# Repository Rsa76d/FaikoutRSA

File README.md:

## Support

You can support this project in many ways, including testing and diagnostics, merge requests, clearly described issues and suggestions, and [buying Faikout boards from us](https://shop.revk.uk?mrlHiG1i). Thank you all for your support. This is open source so others can make and sell (with trademark restrictions). AI based bug reprots or MRs will get you blocked.

# ESP32-Faikout

Everyone knows Daikin make some of the best air conditioners out there, mechanically speaking. Sadly their WiFi control modules are not so good, especially the latest models which are all cloud based, require an internet connection to even work, and are slow.

This code/module provides local control via web interface, MQTT, and HomeAssistant integration, all with no cloud crap.

* There is also a new [Faikout Remote Control](https://remote.revk.uk/) available, BLE linked to the Faikout, with environmental sensors, available now.

I'd like to thank the contributors, but contributions are made and accepted on basis that you issue your contribution under the same GPL licence as the project. Forks are allowed on the basis that your forks are on the same GPL licence as the project.

## Trademark

This is an open source project, but bear in mind you cannot sell boards bearing the Andrews & Arnold Ltd name, the A&A logo, the registered trademark Faikout, the registered trademark AJK logo, or the GS1 allocated EANs assigned to Andrews & Arnold Ltd.

Note the name change from Faikin to Faikout as Daikin complained to Amazon and caused a lot of issues. As such Faikout is now a registered trademark to avoid such issues.

## Further manuals / links

- [Work in progress / release notes](/RevK/ESP32-Faikout/wiki/Work-in-progress)
- [Wiring](/RevK/ESP32-Faikout/wiki/Wiring)
- [Setup](Manuals/Setup.md) Manual
- [Controls](Manuals/Controls.md) Manual
- [Advanced](Manuals/Advanced.md) Manual
- [ESP8266 port](https://github.com/Sonic-Amiga/ESP8266-Faikin) of this code
- [list of supported air-con](/RevK/ESP32-Faikout/wiki/List-of-confirmed-working-air-con-units) WiKi (please update as needed)
- [DoC](Manuals/DoC.md) and Vulnerability disclosure policy
- [S21](Manuals/S21.md) reverse engineered details of `S21` protocol

For support, see issues.

## Safety

Always propely isolate power before opening your air-con. Take care as dangerous voltages. Some connector types have dangerous voltage in operation.

### Ethernet

The Ethernet board has an RJ45 10/100 Ethernet connector for improved reliability and privacy. The Ethernet has an isolating transformer and clearances, but I have to stress **this is a prototype/dev board for specialist/hobbyist use only, and is NOT certified for grid power safety isolation. DO NOT USE WITH X403 CONNECTOR or any connector with dangerous voltages.**

### PoE Ethernet (design not finished)

The PoE Ethernet board has an RJ45 10/100 Ethernet connector for improved reliability and privacy, with PoE power for the Faikout module. The PoE power module has electrical isolation. The board also has opto isolators for the S21 connection, electrically isolating it from the air conditioning unit. This adds extra layers of safety, however I have to stress **this is a prototype/dev board for specialist/hobbyist use only, and is NOT certified for grid power safety isolation.**

Design now works, and boards on order.

## PCB and case

Buy from [shop.revk.uk](https://shop.revk.uk?mrlHiG1i). Also available from a third party in Australia eBay.

New Ethernet option.

New Opto-isiolated PoE Ethernet option.

Board are supplied in a panel, with snap off parts. The basic Faikout board can be two sizes 45x36mm or 40x16mm.

## Why I made this

The history is that, after years of using Daikin air-con in my old home, and using the local http control, in my new house in Wales the WiFi was all cloud based with no local control, and useless, and slow. Just configuring it was a nightmare. I spent all day reverse engineering it and making a new module to provide local control. Pull requests and feature ideas welcome.

This whole project is almost entirely by me, but with some valuable contributions from others (thank you). All of my bits are copyright by me and Andrews & Arnold Ltd who sponsor the whole project, and released under GPL. Whilst not required by the licence, attribution and links would be appreciated if you reuse this.

## How to get one

But also, the PCB designs are published, including production files for [JLCPCB](https://jlcpcb.com). You need to remove trademarks, etc, and you would also need something to program them (TC2030 lead). Obviously you need some experience with PCB ordering and diagnostics if getting your own boards made.

# Set-up

Appears as access point with simple web page to set up on local WiFI. On iPhone the setup page auto-loads.

# Operation

Local interactive web control page using *hostname*.local, no app required, no external internet required.

- [Setup](Manuals/Setup.md) Manual
- [Controls](Manuals/Controls.md) Manual
- [Advanced](Manuals/Advanced.md) Manual

# Design

* KiCad PCB designs included, with JLCPCB production files
* 3D printed case STL files
* Documentation of reverse engineered protocol included

Basically, Daikin have gone all cloudy with the latest WiFi controllers. This module is designed to provide an alternative.

* Simple local web based control with live websocket status, easy to save as desktop icon on a mobile phone
* MQTT reporting and controls
* Works with Home Assistant over MQTT - note Home Assistant can work with HomeKit
* Includes linux mysql/mariadb based logging and graphing tools
* Works with [EnvMon](https://codeberg.org/RevK/ESP32-EnvMon) Environmental Monitor for finer control and status display
* or, works with BlueCoinT and Telink [BLE temperature sensor](Manuals/BLE.md) as a remote reference in an auto mode
* Automatically works out if S21 or X50 protocol (used on bigger/ducted units)
* Backwards compatible direct `/aircon/...` URLs

# Building code yourself

Git clone this `--recursive` to get all the submodules, and it should build with just `make`. There are make targets for other variations, but this hardware is the `make pico` or `make s3` version. The `make` actually runs the normal `idf.py` to build which then uses cmake. `make menuconfig` can be used to fine tune the settings, but the defaults should be mostly sane. `make flash` should work to program. If flashing yourself, you will need a programming lead, e.g. [Tazmotizer](https://codeberg.org/RevK/Tasmotizer-PCB) or similar, and of course the full ESP IDF environment. The latest boards also have 4 pads for direct USB connection to flash with no adaptor. The modules on Amazon come pre-loaded and can upgrade over the air.

The code is normally set up to automatically upgrade the software, checking roughly once a week. You can change this in settings via MQTT.

If you build yourself, you either need no code signing, or your own signing key. This will break auto-updates which try to load my code releases, so you need to adjuist settings `otahost` and `otaauto` accordingly. You can set these in the build config, along with WiFi settings, etc.

## Flashing code

You will need to connect a suitable programming lead. Boards have a tag-connect compatible header for a [TC2030-USB-NL](https://www.tag-connect.com/product/tc2030-usb-nl) lead. Note that the latest boards have test pads on the back which include USB, so you can solder a USB lead if necessary.

See [https://codeberg.org/RevK/ESP32-RevK](https://codeberg.org/RevK/ESP32-RevK) for more details of how to flash the files easily.

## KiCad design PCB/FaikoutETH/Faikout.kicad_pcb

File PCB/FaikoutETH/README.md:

# FaikoutETH

## Trademark

This project is subject to the licence in the LICENCE file, and even if that says it is an open source project, you cannot sell boards or cases bearing the Andrews & Arnold Ltd name, the A&A logo, the registered trademark AJK logo, or other registered trademarks, or any GS1 allocated EANs/barcode assigned to Andrews & Arnold Ltd.

## PCB Designs

These files are for use with [KiCAD](https://www.kicad.org).

- [Faikout](Faikout.kicad_pro)

## 3D

3D case designs are normally automatically created from the PCB so as to ensure correct details and placement of apertures, etc.

|Design|Bottom|Top|Combined|
|------|------|---|--------|
|Faikout||||

## PCB Images Faikout

---

*Auto generated README.md 2026-10-09T09:55:18*

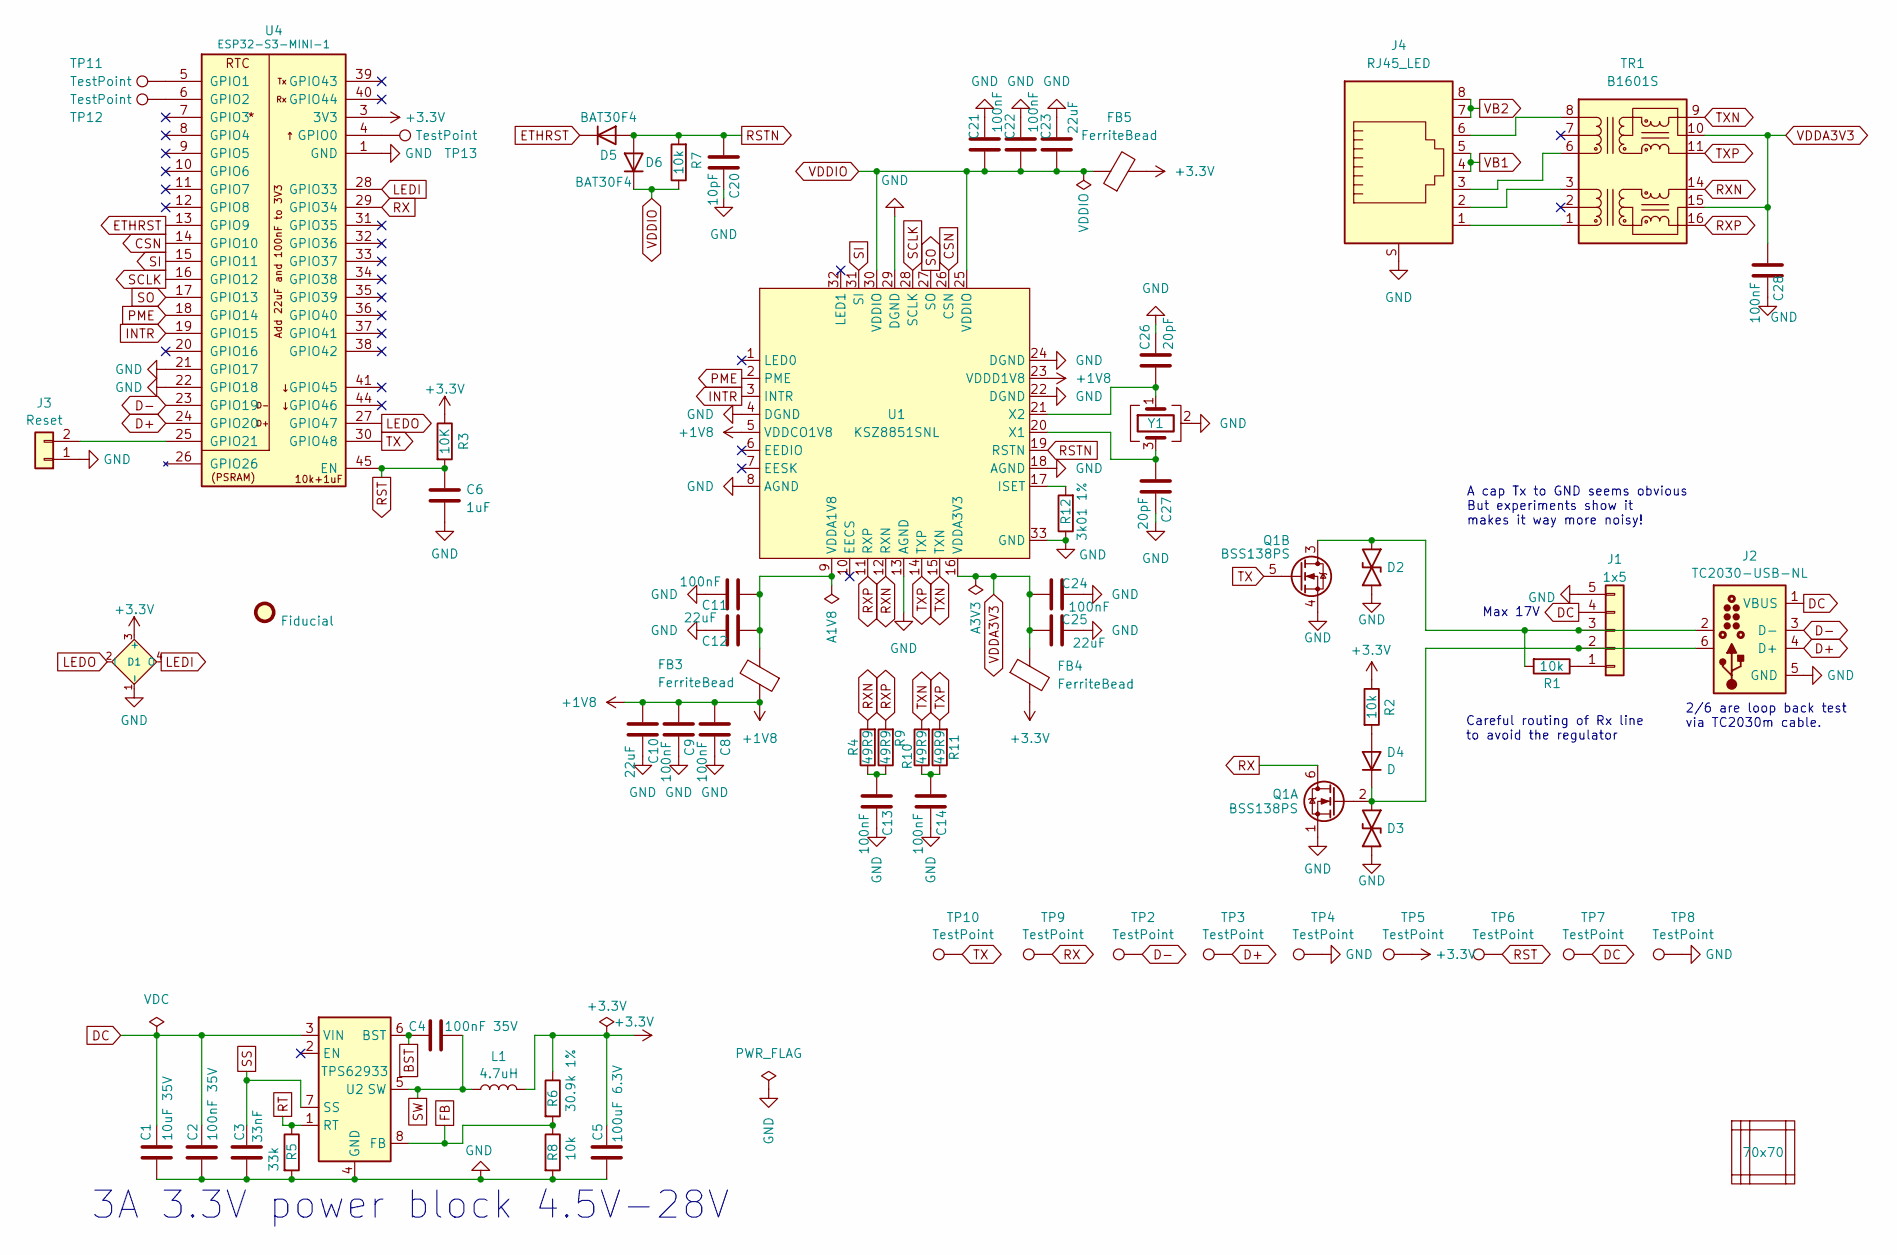
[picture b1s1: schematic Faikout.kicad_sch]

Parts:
C1: 10uF 35V; C_0603; MPN C22367827
C2, C4: 100nF 35V; C_0201; MPN C181043
C3: 33nF; C_0201; MPN C5142554
C5: 100uF 6.3V; C_0805; MPN C141660
C6: 1uF; C_0201; MPN C87143
C8, C9, C11, C13, C14, C21, C22, C24, C28: 100nF; C_0201; MPN C66938
C10, C12, C23, C25: 22uF; C_0402; MPN C105226
C20: 10pF; C_0201; MPN C76921
C26, C27: 20pF; C_0201; MPN C71879
D1: XL-1615RGBC-2812B; SMD1615; MPN C5349954
D2, D3: DFN1006-2L; MPN C5137770
D4: D; D_0402; MPN C28642302
D5, D6: BAT30F4; D_0201; MPN C18197832
FB3, FB4, FB5: FerriteBead; L_0603; MPN C14709
FID2: Fiducial; Fiducial_1mm_Mask2mm
J1: 1x5; JST_EH_S5B-EH_1x05_P2.50mm_Horizontal; MPN C265103
J2: TC2030-USB-NL; Tag-Connect_TC2030-IDC-NL_2x03_P1.27mm_Vertical
J3: Reset; AA-Pad
J4: RJ45_LED; RC01516; MPN C708636
L1: 4.7uH; L_6x6; MPN C32684
PCB1: 70x70; PCB7070
Q1: BSS138PS; SOT-363_SC-70-6; MPN C193381
R1, R2, R7: 10k; R_0201; MPN C138117
R3: 10K; R_0201; MPN C138117
R4, R9, R10, R11: 49R9; R_0201; MPN C100141
R5: 33k; R_0201; MPN C473534
R6: 30.9k 1%; R_0201; MPN C473585
R8: 10k; R_0201; MPN C106225
R12: 3k01 1%; R_0201; MPN C320817
TP2, TP3, TP4, TP5, TP6, TP7, TP8, TP9, TP10, TP11, TP12, TP13: TestPoint; PAD-2mm
TR1: B1601S; MPN C510548
U1: KSZ8851SNL; QFN-32-1EP_5x5mm_P0.5mm_EP3.7x3.7mm-hot; MPN C633272
U2: TPS62933; SOT-583-8; MPN C3200405
U4: ESP32-S3-MINI-1; MPN C3013941
V3, V4, V5, V6, V7: VCUT70N
Y1: Crystal_GND24; Crystal-3.2x2.5; MPN C5155480

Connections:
+1V8: C8.1, C9.1, C10.1, FB3.1, U1.5 (VDDCO1V8), U1.23 (VDDD1V8)
+3.3V: C5.1, D1.3 (+), FB4.2, FB5.2, L1.2, R2.1, R3.1, R6.1, TP5.1 (1_1), U4.3 (3V3)
BST: C4.1, U2.6 (BST)
CSN: U1.26 (CSN), U4.14 (GPIO10)
D+: J2.4 (D+), TP3.1 (1_1), U4.24 (GPIO20)
D-: J2.3 (D-), TP2.1 (1_1), U4.23 (GPIO19)
DC: C1.1, C2.1, J1.4, J2.1 (VBUS), TP7.1 (1_1), U2.3 (VIN)
ETHRST: D5.1 (K), U4.13 (GPIO9)
FB: R6.2, R8.1, U2.8 (FB)
GND: C1.2, C2.2, C3.2, C5.2, C6.2, C8.2, C9.2, C10.2, C11.2, C12.2, C13.2, C14.2, C20.2, C21.2, C22.2, C23.2, C24.2, C25.2, C26.2, C27.2, C28.2, D1.1 (-), D2.1, D3.1, J1.5, J2.5 (GND), J3.1, J4.S, Q1.1 (SN), Q1.4 (DP), R5.2, R8.2, R12.1, TP4.1 (1_1), TP8.1 (1_1), U1.4 (DGND), U1.8 (AGND), U1.13 (AGND), U1.18 (AGND), U1.22 (DGND), U1.24 (DGND), U1.29 (DGND), U1.33 (GND), U2.4 (GND), U4.1 (GND), U4.2 (GND), U4.21 (GPIO17), U4.22 (GPIO18), U4.42 (GND), U4.43 (GND), U4.46 (GND), U4.47 (GND), U4.48 (GND), U4.49 (GND), U4.50 (GND), U4.51 (GND), U4.52 (GND), U4.53 (GND), U4.54 (GND), U4.55 (GND), U4.56 (GND), U4.57 (GND), U4.58 (GND), U4.59 (GND), U4.60 (GND), U4.61 (GND), U4.62 (GND), U4.63 (GND), U4.64 (GND), U4.65 (GND), Y1.2 (G), Y1.4 (G)
INTR: U1.3 (INTR), U4.19 (GPIO15)
LEDI: D1.4 (O), U4.28 (GPIO33)
LEDO: D1.2 (I), U4.27 (GPIO47)
unnamed: C13.1, R4.1, R9.1
unnamed: C14.1, R10.1, R11.1
unnamed: D4.2 (A), R2.2
unnamed: D3.2, D4.1 (K), J1.2, J2.6, Q1.2 (GN)
unnamed: J1.1, R1.1
unnamed: D2.2, J1.3, J2.2, Q1.3 (SP), R1.2
unnamed: J3.2, U4.25 (GPIO21)
unnamed: J4.3, TR1.6 (RD+)
unnamed: J4.6, TR1.8 (RD-)
unnamed: J4.1, TR1.1 (TD+)
unnamed: J4.2, TR1.3 (TD-)
unnamed: R12.2, U1.17 (ISET)
unnamed: C11.1, C12.1, FB3.2, U1.9 (VDDA1V8)
unnamed: C27.1, U1.20 (X1), Y1.3
unnamed: C26.1, U1.21 (X2), Y1.1
unnamed: TP13.1 (1_1), U4.4 (GPIO0)
unnamed: TP11.1 (1_1), U4.5 (GPIO1)
unnamed: TP12.1 (1_1), U4.6 (GPIO2)
PME: U1.2 (PME), U4.18 (GPIO14)
RST: C6.1, R3.2, TP6.1 (1_1), U4.45 (EN)
RSTN: C20.1, D5.2 (A), D6.2 (A), R7.2, U1.19 (RSTN)
RT: R5.1, U2.1 (RT)
RX: Q1.6 (DN), TP9.1 (1_1), U4.29 (GPIO34)
RXN: R4.2, TR1.14 (TX-), U1.12 (RXN)
RXP: R9.2, TR1.16 (TX+), U1.11 (RXP)
SCLK: U1.28 (SCLK), U4.16 (GPIO12)
SI: U1.31 (SI), U4.15 (GPIO11)
SO: U1.27 (SO), U4.17 (GPIO13)
SS: C3.1, U2.7 (SS)
SW: C4.2, L1.1, U2.5 (SW)
TX: Q1.5 (GP), TP10.1 (1_1), U4.30 (GPIO48)
TXN: R10.2, TR1.9 (RX-), U1.15 (TXN)
TXP: R11.2, TR1.11 (RX+), U1.14 (TXP)
VB1: J4.4, J4.5
VB2: J4.7, J4.8
VDDA3V3: C24.1, C25.1, C28.1, FB4.1, TR1.10 (C_RX), TR1.15 (C_TX), U1.16 (VDDA3V3)
VDDIO: C21.1, C22.1, C23.1, D6.1 (K), FB5.1, R7.1, U1.25 (VDDIO), U1.30 (VDDIO)

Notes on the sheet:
Careful routing of Rx line to avoid the regulator
Max 17V
2/6 are loop back test via TC2030m cable.
A cap Tx to GND seems obvious But experiments show it makes it way more noisy!
3A 3.3V power block 4.5V-28V

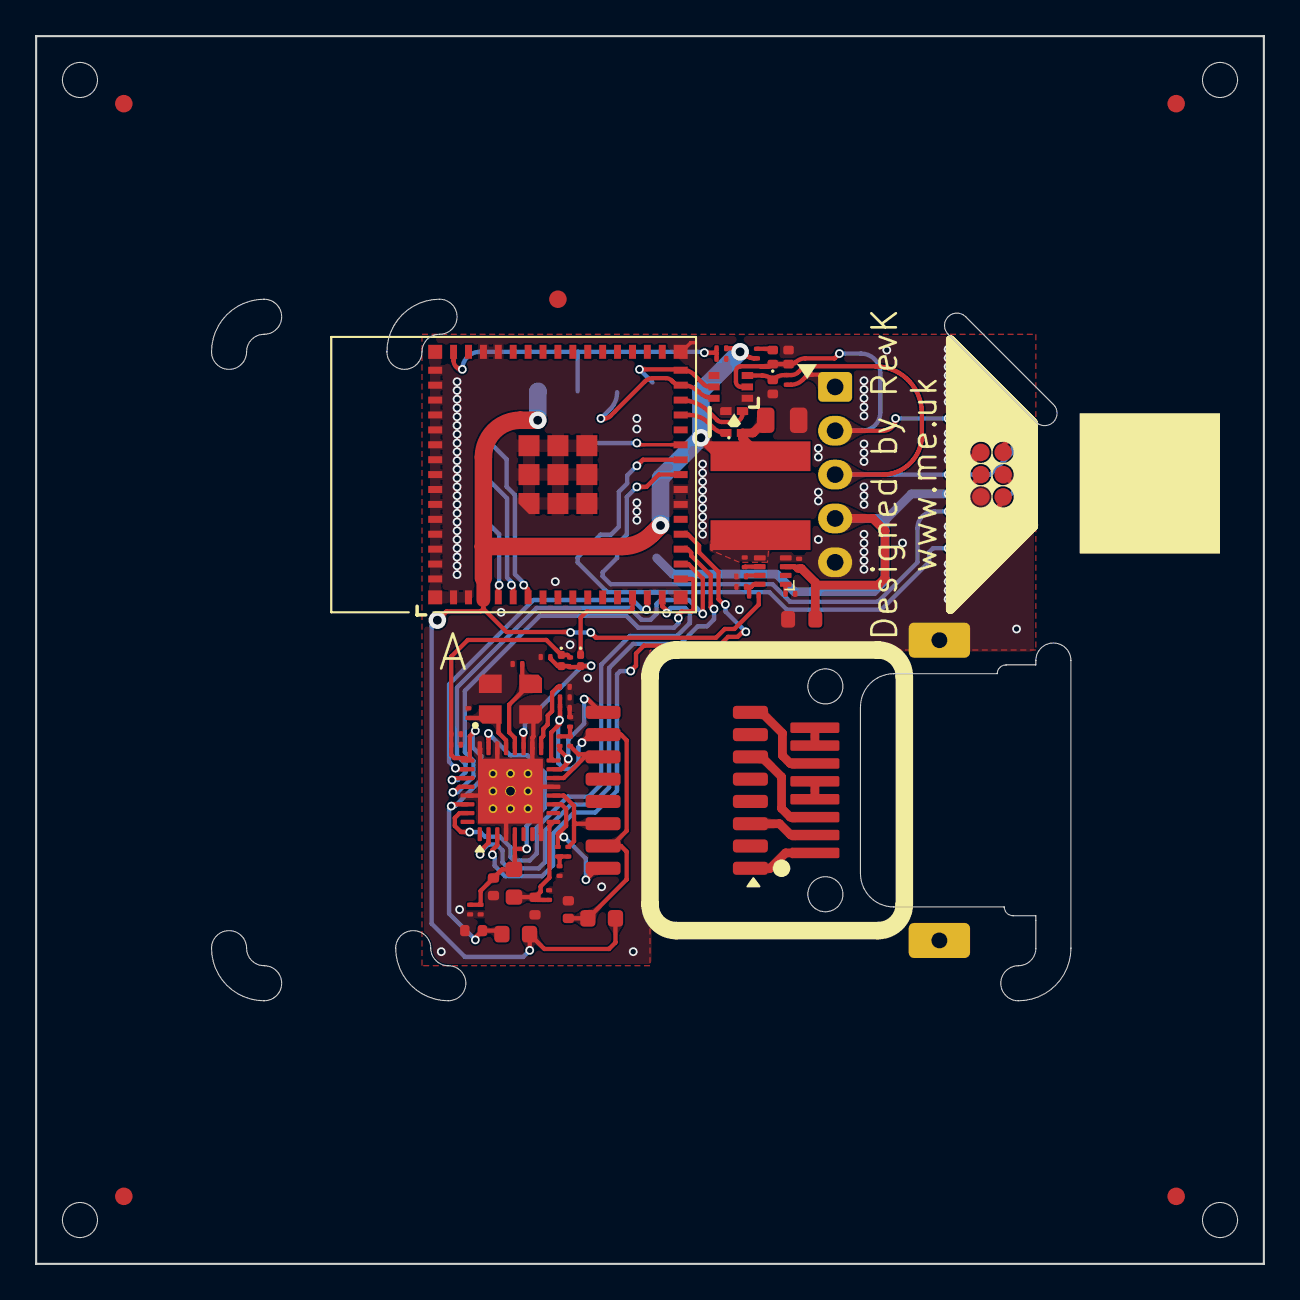
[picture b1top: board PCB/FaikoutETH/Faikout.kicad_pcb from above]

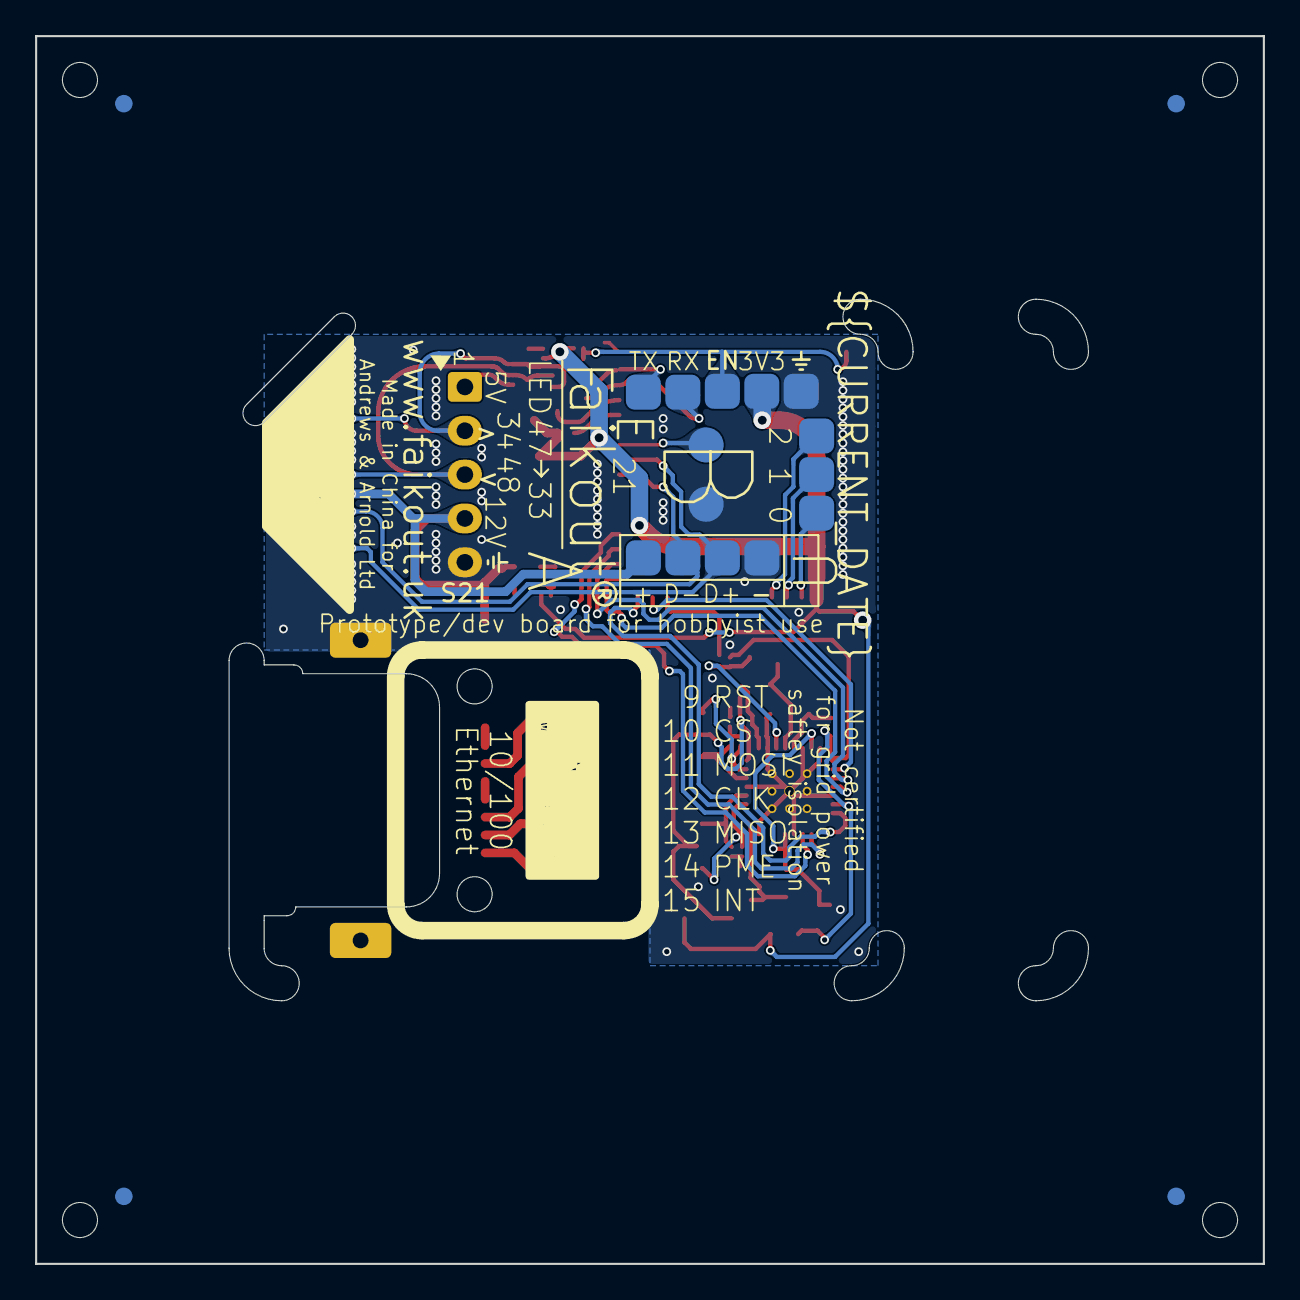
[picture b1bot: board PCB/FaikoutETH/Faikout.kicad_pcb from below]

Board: 2 copper layers, 70.0 x 70.0 mm, 73 parts (14 on the bottom side), 50 nets.

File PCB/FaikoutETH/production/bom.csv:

Designator,Footprint,Quantity,Value,LCSC Part #
C1,C_0603,1,10uF 35V,C22367827
"C10, C12, C23, C25",C_0402,4,22uF,C105226
"C11, C13, C14, C21, C22, C24, C28, C8, C9",C_0201,9,100nF,C66938
"C2, C4",C_0201,2,100nF 35V,C181043
C20,C_0201,1,10pF,C76921
"C26, C27",C_0201,2,20pF,C71879
C3,C_0201,1,33nF,C5142554
C5,C_0805,1,100uF 6.3V,C141660
C6,C_0201,1,1uF,C87143
D1,SMD1615,1,XL-1615RGBC-2812B,C5349954
"D2, D3",DFN1006-2L,2,~,C5137770
D4,D_0402,1,D,C28642302
"D5, D6",D_0201,2,BAT30F4,C18197832
"FB3, FB4, FB5",L_0603,3,FerriteBead,C14709
J1,JST_EH_S5B-EH_1x05_P2.50mm_Horizontal,1,1x5,C265103
J4,RC01516,1,RJ45_LED,C708636
L1,L_6x6,1,4.7uH,C32684
Q1,SOT-363_SC-70-6,1,BSS138PS,C193381
"R1, R2, R3, R7",R_0201,4,10k,C138117
"R10, R11, R4, R9",R_0201,4,49R9,C100141
R12,R_0201,1,3k01 1%,C320817
R5,R_0201,1,33k,C473534
R6,R_0201,1,30.9k 1%,C473585
R8,R_0201,1,10k,C106225
TR1,B1601S,1,B1601S,C510548
U1,QFN-32-1EP_5x5mm_P0.5mm_EP3.7x3.7mm-hot,1,KSZ8851SNL,C633272
U2,SOT-583-8,1,TPS62933,C3200405
U4,ESP32-S3-MINI-1,1,ESP32-S3-MINI-1,C3013941
Y1,Crystal-3.2x2.5,1,Crystal_GND24,C5155480

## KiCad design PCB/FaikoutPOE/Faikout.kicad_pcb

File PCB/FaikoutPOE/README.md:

# FaikoutPOE

## Trademark

This project is subject to the licence in the LICENCE file, and even if that says it is an open source project, you cannot sell boards or cases bearing the Andrews & Arnold Ltd name, the A&A logo, the registered trademark AJK logo, or other registered trademarks, or any GS1 allocated EANs/barcode assigned to Andrews & Arnold Ltd.

## PCB Designs

These files are for use with [KiCAD](https://www.kicad.org).

- [Faikout](Faikout.kicad_pro)

## 3D

3D case designs are normally automatically created from the PCB so as to ensure correct details and placement of apertures, etc.

|Design|Bottom|Top|Combined|
|------|------|---|--------|
|Faikout||||

## PCB Images Faikout

---

*Auto generated README.md 2026-10-09T09:56:11*

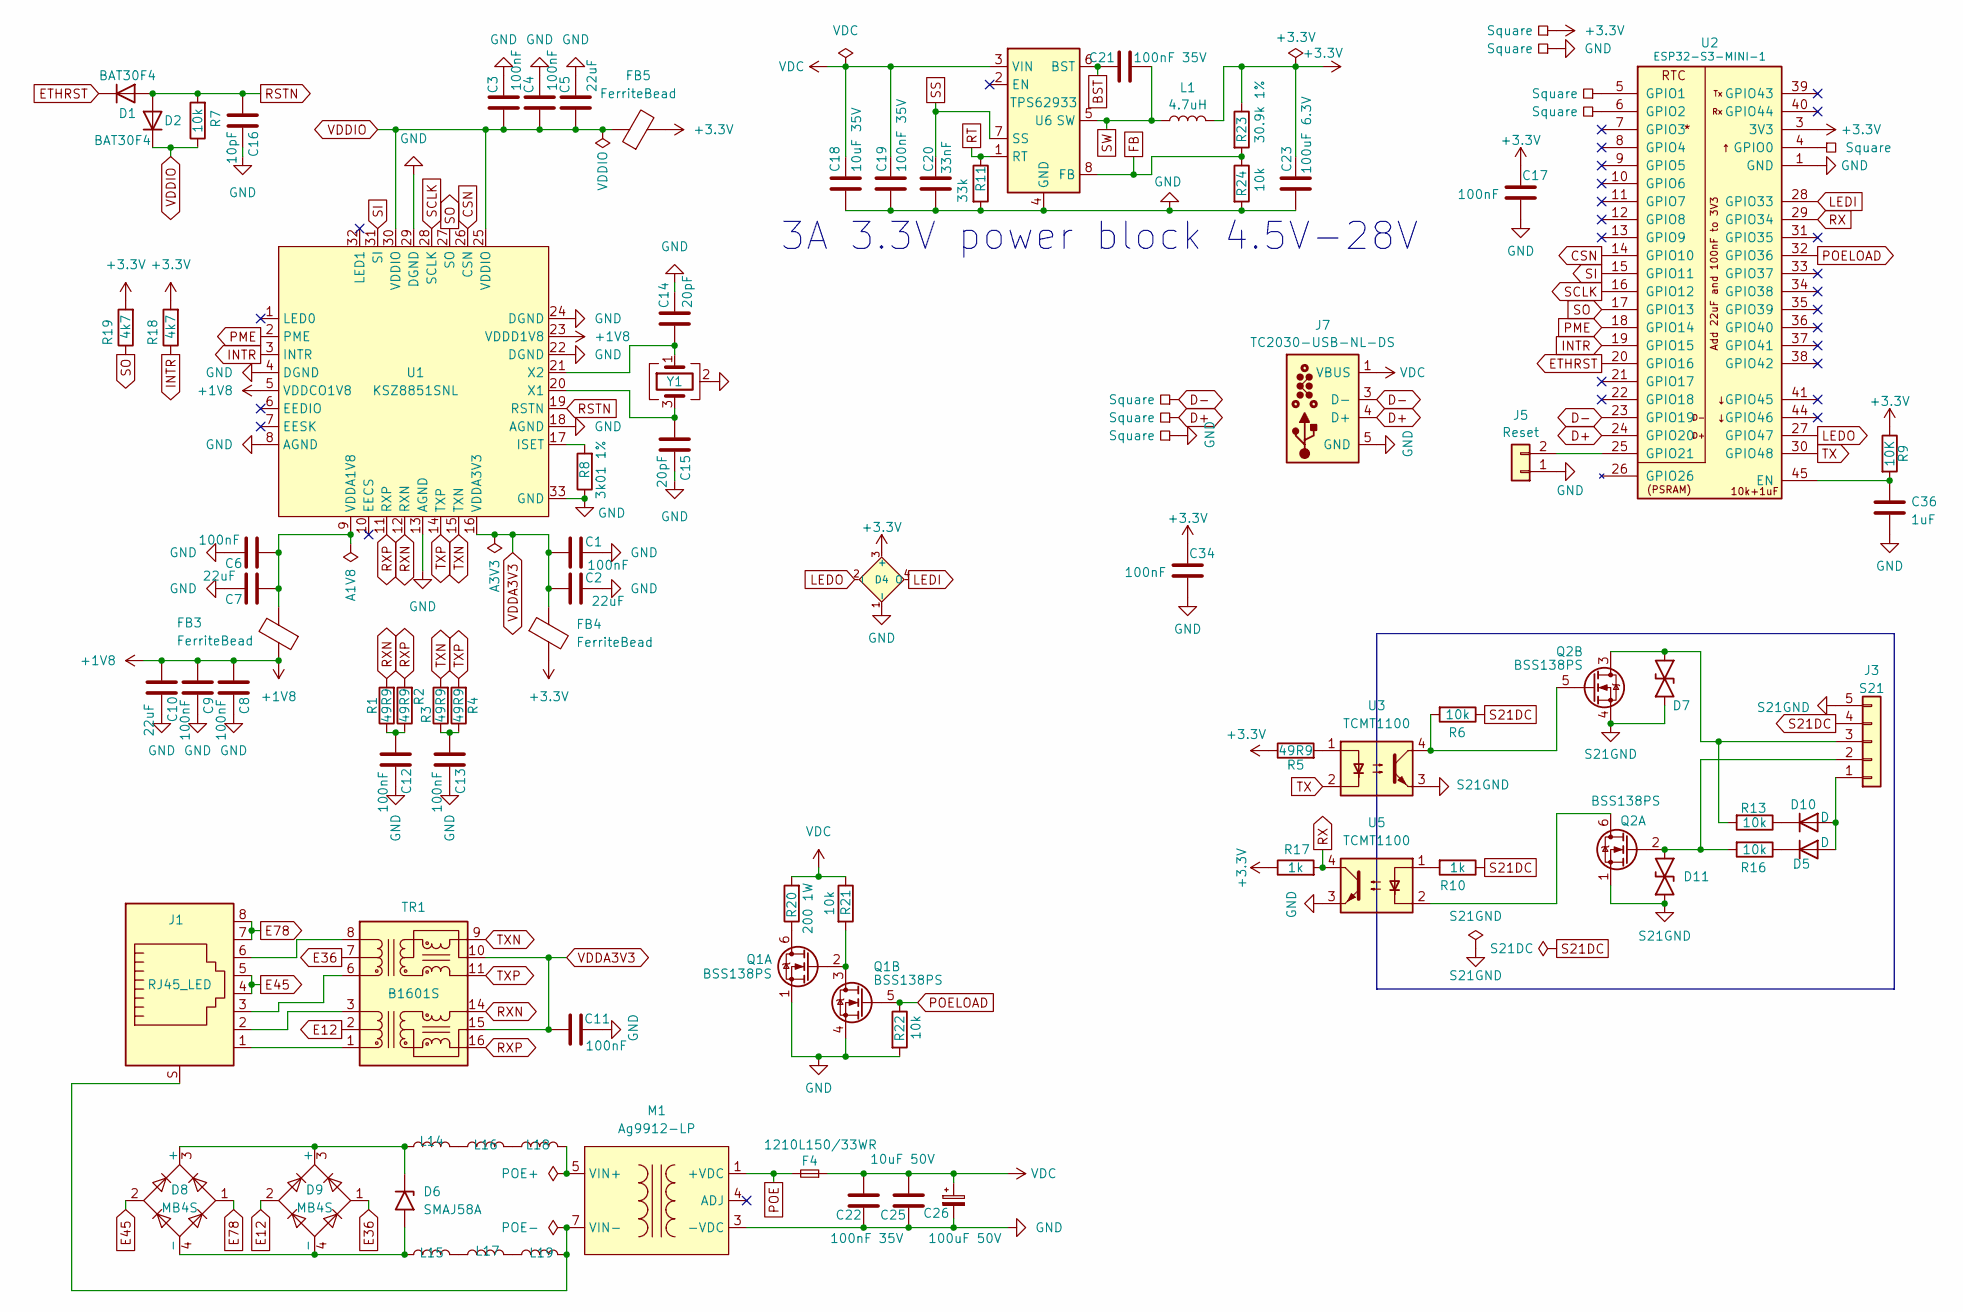
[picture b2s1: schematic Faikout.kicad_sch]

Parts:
C1, C3, C4, C6, C8, C9, C11, C12, C13: 100nF; C_0201; MPN C66938
C2, C5, C7, C10: 22uF; C_0402; MPN C105226
C14, C15: 20pF; C_0201; MPN C71879
C16: 10pF; C_0201; MPN C76921
C17, C34: 100nF; C_0201; MPN C76934
C18: 10uF 35V; C_0603; MPN C22367827
C19, C21, C22: 100nF 35V; C_0201; MPN C181043
C20: 33nF; C_0201; MPN C5142554
C23: 100uF 6.3V; C_0805; MPN C141660
C25: 10uF 50V; C_1206; MPN C13585
C26: 100uF 50V; CP_Elec_6.3x7.7; MPN C72478
C36: 1uF; C_0201
D1, D2: BAT30F4; D_0201; MPN C18197832
D4: XL-1615RGBC-2812B; SMD1615-Side; MPN C5349954
D5, D10: D; D_0402; MPN C28642302
D6: SMAJ58A; D_SMA
D7, D11: DFN1006-2L; MPN C5137770
D8, D9: MB4S; TO-269AA-BR; MPN C232847
F4: 1210L150/33WR; Fuse_1210; MPN C42376299
FB3, FB4, FB5: FerriteBead; L_0603; MPN C14709
J1: RJ45_LED; RC01516; MPN C708636
J3: S21; JST_EH_S5B-EH_1x05_P2.50mm_Horizontal; MPN C265103
J5: Reset; AA-Pad
J7: TC2030-USB-NL-DS; Tag-Connect_TC2030-IDC-NL_2x03_P1.27mm_Vertical
L1: 4.7uH; L_6x6; MPN C32684
L14, L15, L16, L17, L18, L19: CBG201209U121T; L_0805; MPN C41330
M1: Ag9912-LP; Ag9900-LP; MPN C6789853
P1, P2, P3, P4, P5, P6, P7, P8: Square; PAD-2mm
Q1, Q2: BSS138PS; SOT-363_SC-70-6; MPN C193381
R1, R2, R3, R4, R5: 49R9; R_0201; MPN C100141
R6, R7, R13, R16, R21, R22, R24: 10k; R_0201; MPN C106225
R8: 3k01 1%; R_0201; MPN C320817
R9: 10K; R_0201; MPN C106225
R10, R17: 1k; R_0201; MPN C270365
R11: 33k; R_0201; MPN C473534
R18, R19: 4k7; R_0201; MPN C138135
R20: 200 1W; R_2512; MPN C2907575
R23: 30.9k 1%; R_0201; MPN C473585
TR1: B1601S; MPN C510548
U1: KSZ8851SNL; QFN-32-1EP_5x5mm_P0.5mm_EP3.7x3.7mm-hot; MPN C633272
U2: ESP32-S3-MINI-1; MPN C3013941
U3: TCMT1100; SOP-4_4.4x2.6mm_P1.27mm; MPN C118298
U5: TCMT1100; SOP-4_4.4x2.6mm_P1.27mm; MPN MPN
U6: TPS62933; SOT-583-8; MPN C3200405
Y1: Crystal_GND24; Crystal-3.2x2.5; MPN C5155480

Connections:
+1V8: C8.1, C9.1, C10.1, FB3.1, U1.5 (VDDCO1V8), U1.23 (VDDD1V8)
+3.3V: C17.2, C23.1, C34.2, D4.3 (+), FB4.2, FB5.2, L1.2, P7.1 (P_1), R5.1, R9.1, R17.1, R18.2, R19.2, R23.1, U2.3 (3V3)
BST: C21.1, U6.6 (BST)
CSN: U1.26 (CSN), U2.14 (GPIO10)
D+: J7.4 (D+), P3.1 (P_1), U2.24 (GPIO20)
D-: J7.2 (NC), J7.3 (D-), J7.6 (NC), P2.1 (P_1), U2.23 (GPIO19)
E12: D9.2, TR1.2 (C_TD)
E36: D9.1, TR1.7 (C_RD)
E45: D8.2, J1.4, J1.5
E78: D8.1, J1.7, J1.8
ETHRST: D1.1 (K), U2.20 (GPIO16)
FB: R23.2, R24.1, U6.8 (FB)
GND: C1.2, C2.2, C3.2, C4.2, C5.2, C6.2, C7.2, C8.2, C9.2, C10.2, C11.2, C12.2, C13.2, C14.2, C15.2, C16.2, C17.1, C18.2, C19.2, C20.2, C22.2, C23.2, C25.1, C26.2, C34.1, C36.2, D4.1 (-), J5.1, J7.5 (GND), M1.3 (-VDC), P4.1 (P_1), P8.1 (P_1), Q1.1 (SN), Q1.4 (DP), R8.1, R11.2, R22.2, R24.2, U1.4 (DGND), U1.8 (AGND), U1.13 (AGND), U1.18 (AGND), U1.22 (DGND), U1.24 (DGND), U1.29 (DGND), U1.33 (GND), U2.1 (GND), U2.2 (GND), U2.42 (GND), U2.43 (GND), U2.46 (GND), U2.47 (GND), U2.48 (GND), U2.49 (GND), U2.50 (GND), U2.51 (GND), U2.52 (GND), U2.53 (GND), U2.54 (GND), U2.55 (GND), U2.56 (GND), U2.57 (GND), U2.58 (GND), U2.59 (GND), U2.60 (GND), U2.61 (GND), U2.62 (GND), U2.63 (GND), U2.64 (GND), U2.65 (GND), U5.3, U6.4 (GND), Y1.2 (G), Y1.4 (G)
INTR: R18.1, U1.3 (INTR), U2.19 (GPIO15)
LEDI: D4.4 (O), U2.28 (GPIO33)
LEDO: D4.2 (I), U2.27 (GPIO47)
unnamed: C12.1, R1.1, R2.1
unnamed: C13.1, R3.1, R4.1
unnamed: D5.1 (K), R16.1
unnamed: D6.1 (A1), D8.3 (+), D9.3 (+), L14.1
unnamed: D6.2 (A2), D8.4 (-), D9.4 (-), L15.1
unnamed: D5.2 (A), D10.2 (A), J3.1
unnamed: D10.1 (K), R13.1
unnamed: D11.1, J3.2, Q2.2 (GN), R16.2
unnamed: D7.2, J3.3, Q2.3 (SP), R13.2
unnamed: J5.2, U2.25 (GPIO21)
unnamed: L14.2, L16.1
unnamed: L15.2, L17.1
unnamed: L16.2, L18.1
unnamed: L17.2, L19.1
unnamed: P1.1 (P_1), U2.4 (GPIO0)
unnamed: P5.1 (P_1), U2.5 (GPIO1)
unnamed: P6.1 (P_1), U2.6 (GPIO2)
unnamed: Q1.6 (DN), R20.1
unnamed: Q1.2 (GN), Q1.3 (SP), R21.2
unnamed: Q2.6 (DN), U5.2
unnamed: Q2.5 (GP), R6.2, U3.4
unnamed: R5.2, U3.1
unnamed: R10.2, U5.1
unnamed: J1.3, TR1.6 (RD+)
unnamed: J1.6, TR1.8 (RD-)
unnamed: J1.1, TR1.1 (TD+)
unnamed: J1.2, TR1.3 (TD-)
unnamed: R8.2, U1.17 (ISET)
unnamed: C6.1, C7.1, FB3.2, U1.9 (VDDA1V8)
unnamed: C15.1, U1.20 (X1), Y1.3
unnamed: C14.1, U1.21 (X2), Y1.1
unnamed: C36.1, R9.2, U2.45 (EN)
PME: U1.2 (PME), U2.18 (GPIO14)
POE: F4.2, M1.1 (+VDC), M1.2 (+VDC)
POELOAD: Q1.5 (GP), R22.1, U2.32 (GPIO36)
RSTN: C16.1, D1.2 (A), D2.2 (A), R7.2, U1.19 (RSTN)
RT: R11.1, U6.1 (RT)
RX: R17.2, U2.29 (GPIO34), U5.4
RXN: R1.2, TR1.14 (TX-), U1.12 (RXN)
RXP: R2.2, TR1.16 (TX+), U1.11 (RXP)
S21DC: J3.4, R6.1, R10.1
S21GND: D7.1, D11.2, J3.5, Q2.1 (SN), Q2.4 (DP), U3.3
SCLK: U1.28 (SCLK), U2.16 (GPIO12)
SI: U1.31 (SI), U2.15 (GPIO11)
SO: R19.1, U1.27 (SO), U2.17 (GPIO13)
SS: C20.1, U6.7 (SS)
SW: C21.2, L1.1, U6.5 (SW)
TX: U2.30 (GPIO48), U3.2
TXN: R3.2, TR1.9 (RX-), U1.15 (TXN)
TXP: R4.2, TR1.11 (RX+), U1.14 (TXP)
VDC: C18.1, C19.1, C22.1, C25.2, C26.1, F4.1, J7.1 (VBUS), R20.2, R21.1, U6.3 (VIN)
VDDA3V3: C1.1, C2.1, C11.1, FB4.1, TR1.10 (C_RX), TR1.15 (C_TX), U1.16 (VDDA3V3)
VDDIO: C3.1, C4.1, C5.1, D2.1 (K), FB5.1, R7.1, U1.25 (VDDIO), U1.30 (VDDIO)
VIN+: L18.2, M1.5 (VIN+), M1.6 (VIN+)
VIN-: J1.S, L19.2, M1.7 (VIN-), M1.8 (VIN-)

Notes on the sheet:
3A 3.3V power block 4.5V-28V

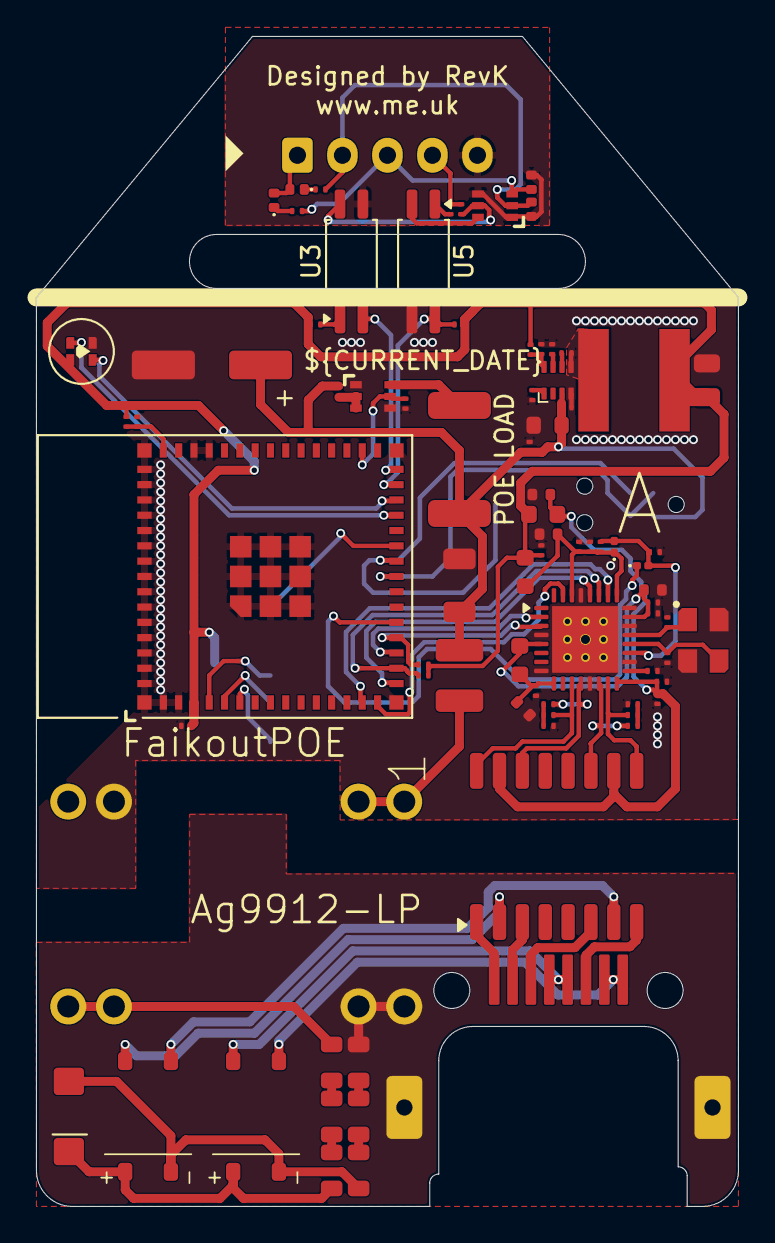
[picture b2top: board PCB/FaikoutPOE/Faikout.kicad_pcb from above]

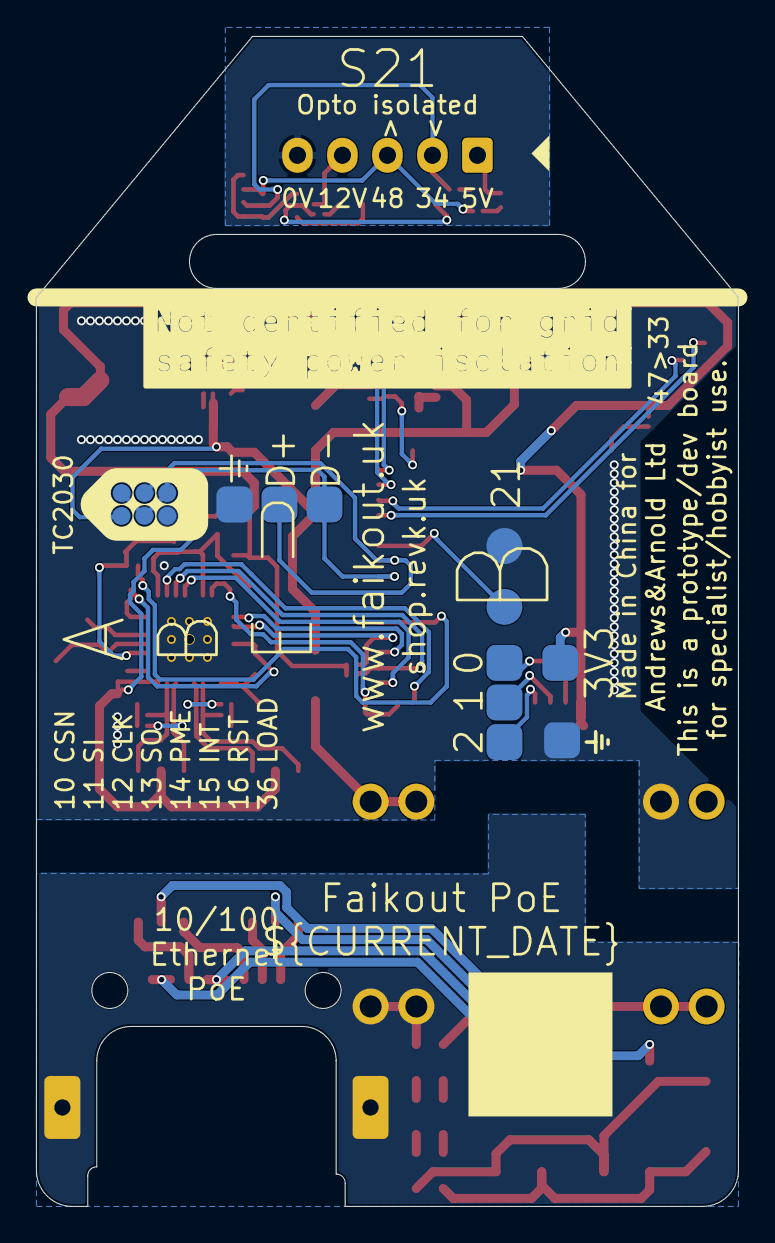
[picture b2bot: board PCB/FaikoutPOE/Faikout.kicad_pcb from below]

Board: 2 copper layers, 39.0 x 65.0 mm, 91 parts (10 on the bottom side), 71 nets.

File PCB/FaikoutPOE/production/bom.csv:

Designator,Footprint,Quantity,Value,LCSC Part #
"C1, C11, C12, C13, C3, C4, C6, C8, C9",C_0201,9,100nF,C66938
"C10, C2, C5, C7",C_0402,4,22uF,C105226
"C14, C15",C_0201,2,20pF,C71879
C16,C_0201,1,10pF,C76921
"C17, C34",C_0201,2,100nF,C76934
C18,C_0603,1,10uF 35V,C22367827
"C19, C21, C22",C_0201,3,100nF 35V,C181043
C20,C_0201,1,33nF,C5142554
C23,C_0805,1,100uF 6.3V,C141660
C25,C_1206,1,10uF 50V,C13585
C26,CP_Elec_6.3x7.7,1,100uF 50V,C72478
C36,C_0201,1,1uF,
"D1, D2",D_0201,2,BAT30F4,C18197832
"D10, D5",D_0402,2,D,C28642302
"D11, D7",DFN1006-2L,2,~,C5137770
D4,SMD1615-Side,1,XL-1615RGBC-2812B,C5349954
D6,D_SMA,1,SMAJ58A,
"D8, D9",TO-269AA-BR,2,MB4S,C232847
F4,Fuse_1210,1,1210L150/33WR,C42376299
"FB3, FB4, FB5",L_0603,3,FerriteBead,C14709
J1,RC01516,1,RJ45_LED,C708636
J3,JST_EH_S5B-EH_1x05_P2.50mm_Horizontal,1,S21,C265103
L1,L_6x6,1,4.7uH,C32684
"L14, L15, L16, L17, L18, L19",L_0805,6,CBG201209U121T,C41330
M1,Ag9900-LP,1,Ag9912-LP,C6789853
"Q1, Q2",SOT-363_SC-70-6,2,BSS138PS,C193381
"R1, R2, R3, R4, R5",R_0201,5,49R9,C100141
"R10, R17",R_0201,2,1k,C270365
R11,R_0201,1,33k,C473534
"R13, R16, R21, R22, R24, R6, R7, R9",R_0201,8,10k,C106225
"R18, R19",R_0201,2,4k7,C138135
R20,R_2512,1,200 1W,C2907575
R23,R_0201,1,30.9k 1%,C473585
R8,R_0201,1,3k01 1%,C320817
TR1,B1601S,1,B1601S,C510548
U1,QFN-32-1EP_5x5mm_P0.5mm_EP3.7x3.7mm-hot,1,KSZ8851SNL,C633272
U2,ESP32-S3-MINI-1,1,ESP32-S3-MINI-1,C3013941
U3,SOP-4_4.4x2.6mm_P1.27mm,1,TCMT1100,C118298
U5,SOP-4_4.4x2.6mm_P1.27mm,1,TCMT1100,MPN
U6,SOT-583-8,1,TPS62933,C3200405
Y1,Crystal-3.2x2.5,1,Crystal_GND24,C5155480

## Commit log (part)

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2026-04-22 fix(ha): use correct MQTT discovery type for demand entity
    HA MQTT discovery topic used 'sellightbulb' as component type,
    which is not a valid HA discovery type. HA silently ignores the
    message and the demand entity does not appear in Home Assistant.
    Changed to 'select', which matches the entity structure already
    in place (options 30-100 in steps of 5, cmd_t, stat_t, val_tpl).
2026-05-20 Beta
2026-05-20 BLE mutex
2026-05-26 autob re-enabled
2026-05-26 Change udp_discovery to udpdiscovery to be consistent, as no other use of _ in settings
2026-05-26 Library update
2026-05-27 Legacy setting could set swing modes not in ise
2026-05-27 noswing tweaks
2026-06-05 ESP IDF v6 update
2026-06-06 Cleaner defaults
2026-06-06 Removed pico as not building on ESP IDF v6 at present (may be possible in time)
2026-06-06 ESP IDF v6
2026-06-10 Gerbers
2026-06-11 new ETH
2026-06-11 web: reap dead WebSocket sockets to fix permanent web-server wedge
    On a marginal link, abandoned /status WebSocket sessions (closed tab or lost link with no clean FIN) were never reclaimed: the async send return was ignored and there was no TCP keep-alive, so each d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
2026-06-12 Testing
2026-06-12 Start on ethernet
2026-06-12 Ethernet board
2026-06-12 Ethernet case
2026-06-12 Fix case
2026-06-12 GPIO clash
2026-06-13 ETH board
2026-06-13 library
2026-06-13 Added POE (not finished)
2026-06-13 POE board
2026-06-13 New PCB
2026-06-13 Release
2026-06-14 New models for RJ45
2026-06-14 Re render
2026-06-14 Started on POE
2026-06-14 Case tweak
2026-06-14 PoE layout, not tracked yet
2026-06-14 Tidy
2026-06-15 POELOAD
2026-06-15 Tweaks
2026-06-18 Tidy models
2026-06-19 Change OTA
2026-06-19 Fix case size, ejit
2026-06-19 Render
2026-06-19 Clerance
2026-06-19 Missing
2026-06-20 Tweak case
2026-06-20 Re render, URL added to case
2026-06-21 Handle B from G1
2026-06-21 Rotate
2026-06-22 Revised case cut
2026-06-22 Tweak edges
2026-06-24 Common httpd config from revk library
2026-06-24 RevK library update (common httpd config)
2026-06-24 new layout
2026-06-25 Adjusted RJ45
2026-06-25 New footprint
2026-06-25 Fan order in HA
2026-06-25 Fan fix
2026-06-25 Manifest
2026-06-25 Adjust manifest
2026-06-26 https
2026-06-29 Tweak design
2026-06-29 New regulator
2026-06-29 As ordered
2026-06-29 Started POE
2026-06-30 Progress
2026-06-30 Fix render
2026-06-30 More tracking
